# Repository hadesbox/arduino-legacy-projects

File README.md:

# arduino-legacy-projects
This repo is a backup of all my old arduino projects

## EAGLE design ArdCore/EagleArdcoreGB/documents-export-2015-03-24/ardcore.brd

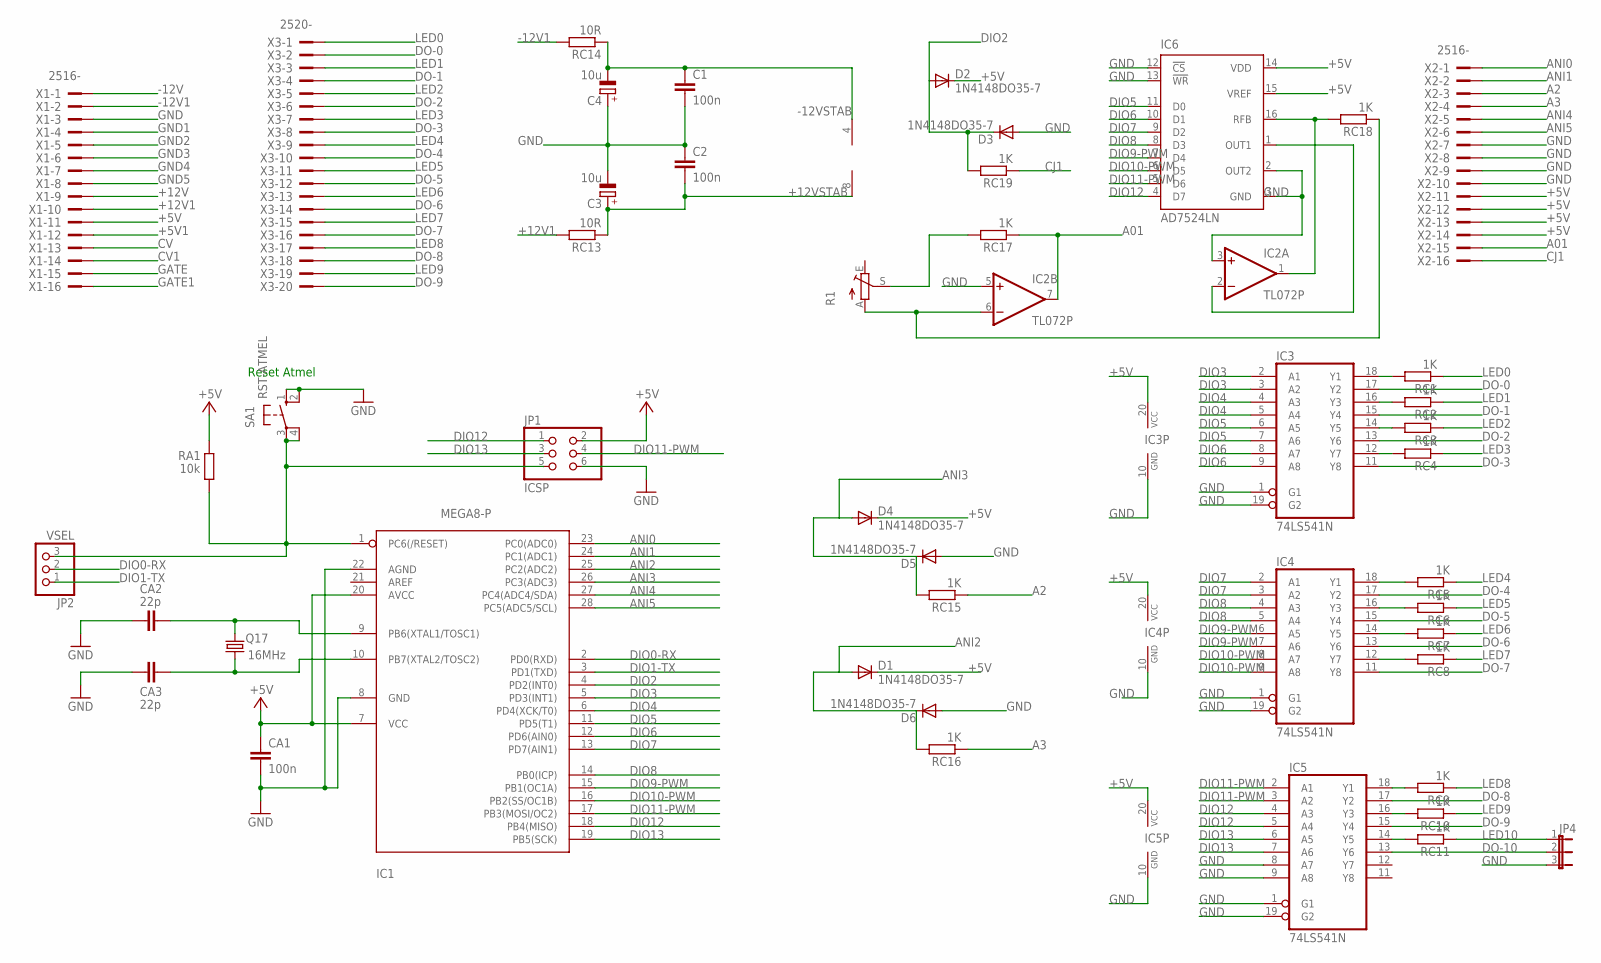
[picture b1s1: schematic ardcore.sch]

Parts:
C1, C2: 100n; C050-025X075
C3, C4: 10u; E2,5-7
CA1: 100n; C050-025X075
CA2, CA3: 22p; C050-025X075
D1, D2, D3, D4, D5, D6: 1N4148DO35-7; DO35-7
IC1: MEGA8-P; DIL28-3
IC2: TL072P; DIL08
IC3, IC4, IC5: 74LS541N; DIL20
IC6: AD7524LN; DIL16
JP1: ICSP; 2X03
JP2: VSEL; 1X03
JP4: JP2E; JP2
Q17: 16MHz; HC49/S
R1: TRIM_EU-B64Y; B64Y
RA1: 10k; 0207/10
RC1, RC2, RC3, RC4, RC5, RC6, RC7, RC8, RC9, RC10, RC11, RC15, RC16, RC17, RC18, RC19: 1K; 0207/10
RC13, RC14: 10R; 0207/10
SA1: RST-ATMEL; B3F-10XX
X1, X2: 2516-; PAK100/2500-16
X3: 2520-; PAK100/2500-20

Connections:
+5V: CA1.1, D1.C, D2.C, D4.C, IC1.7 (VCC), IC1.20 (AVCC), IC3.20 (VCC), IC4.20 (VCC), IC5.20 (VCC), IC6.14 (VDD), IC6.15 (VREF), JP1.2, RA1.1, X1.11, X2.11, X2.12, X2.13, X2.14
+5V1: X1.12
+12V: X1.9
+12V1: RC13.2, X1.10
+12VSTAB: C2.2, C3.+, IC2.8 (V+), RC13.1
-12V: X1.1
-12V1: RC14.2, X1.2
-12VSTAB: C1.1, C4.-, IC2.4 (V-), RC14.1
A01: IC2.7 (OUT), RC17.1, X2.15
A2: RC15.1, X2.3
A3: RC16.1, X2.4
ANI0: IC1.23 (PC0(ADC0)), X2.1
ANI1: IC1.24 (PC1(ADC1)), X2.2
ANI2: D1.A, D6.C, IC1.25 (PC2(ADC2)), RC16.2
ANI3: D4.A, D5.C, IC1.26 (PC3(ADC3)), RC15.2
ANI4: IC1.27 (PC4(ADC4/SDA)), X2.5
ANI5: IC1.28 (PC5(ADC5/SCL)), X2.6
CJ1: RC19.1, X2.16
CV: X1.13
CV1: X1.14
DIO0-RX: IC1.2 (PD0(RXD)), JP2.2
DIO1-TX: IC1.3 (PD1(TXD)), JP2.1
DIO2: D2.A, D3.C, IC1.4 (PD2(INT0)), RC19.2
DIO3: IC1.5 (PD3(INT1)), IC3.2 (A1), IC3.3 (A2)
DIO4: IC1.6 (PD4(XCK/T0)), IC3.4 (A3), IC3.5 (A4)
DIO5: IC1.11 (PD5(T1)), IC3.6 (A5), IC3.7 (A6), IC6.11 (D0)
DIO6: IC1.12 (PD6(AIN0)), IC3.8 (A7), IC3.9 (A8), IC6.10 (D1)
DIO7: IC1.13 (PD7(AIN1)), IC4.2 (A1), IC4.3 (A2), IC6.9 (D2)
DIO8: IC1.14 (PB0(ICP)), IC4.4 (A3), IC4.5 (A4), IC6.8 (D3)
DIO9-PWM: IC1.15 (PB1(OC1A)), IC4.6 (A5), IC4.7 (A6), IC6.7 (D4)
DIO10-PWM: IC1.16 (PB2(SS/OC1B)), IC4.8 (A7), IC4.9 (A8), IC6.6 (D5)
DIO11-PWM: IC1.17 (PB3(MOSI/OC2)), IC5.2 (A1), IC5.3 (A2), IC6.5 (D6), JP1.4
DIO12: IC1.18 (PB4(MISO)), IC5.4 (A3), IC5.5 (A4), IC6.4 (D7), JP1.1
DIO13: IC1.19 (PB5(SCK)), IC5.6 (A5), IC5.7 (A6), JP1.3
DO-0: IC3.17 (Y2), X3.2
DO-1: IC3.15 (Y4), X3.4
DO-2: IC3.13 (Y6), X3.6
DO-3: IC3.11 (Y8), X3.8
DO-4: IC4.17 (Y2), X3.10
DO-5: IC4.15 (Y4), X3.12
DO-6: IC4.13 (Y6), X3.14
DO-7: IC4.11 (Y8), X3.16
DO-8: IC5.17 (Y2), X3.18
DO-9: IC5.15 (Y4), X3.20
DO-10: IC5.13 (Y6), JP4.2
GATE: X1.15
GATE1: X1.16
GND: C1.2, C2.1, C3.-, C4.+, CA1.2, CA2.2, CA3.2, D3.A, D5.A, D6.A, IC1.8 (GND), IC1.22 (AGND), IC2.3 (+IN), IC2.5 (+IN), IC3.1 (G1), IC3.10 (GND), IC3.19 (G2), IC4.1 (G1), IC4.10 (GND), IC4.19 (G2), IC5.1 (G1), IC5.8 (A7), IC5.9 (A8), IC5.10 (GND), IC5.19 (G2), IC6.2 (OUT2), IC6.3 (GND), IC6.12 (!CS), IC6.13 (!WR), JP1.6, JP4.3, SA1.1 (S), SA1.2 (S1), X1.3, X2.7, X2.8, X2.9, X2.10
GND1: X1.4
GND2: X1.5
GND3: X1.6
GND4: X1.7
GND5: X1.8
LED0: RC1.1, X3.1
LED1: RC2.1, X3.3
LED2: RC3.1, X3.5
LED3: RC4.1, X3.7
LED4: RC5.1, X3.9
LED5: RC6.1, X3.11
LED6: RC7.1, X3.13
LED7: RC8.1, X3.15
LED8: RC9.1, X3.17
LED9: RC10.1, X3.19
LED10: JP4.1, RC11.1
unnamed: IC3.18 (Y1), RC1.2
unnamed: IC3.16 (Y3), RC2.2
unnamed: IC3.14 (Y5), RC3.2
unnamed: CA2.1, IC1.9 (PB6(XTAL1/TOSC1)), Q17.2
unnamed: CA3.1, IC1.10 (PB7(XTAL2/TOSC2)), Q17.1
unnamed: IC3.12 (Y7), RC4.2
unnamed: IC4.18 (Y1), RC5.2
unnamed: IC4.16 (Y3), RC6.2
unnamed: IC4.14 (Y5), RC7.2
unnamed: IC4.12 (Y7), RC8.2
unnamed: IC5.18 (Y1), RC9.2
unnamed: IC5.16 (Y3), RC10.2
unnamed: IC5.14 (Y5), RC11.2
unnamed: IC2.6 (-IN), R1.A, RC18.1
unnamed: IC2.2 (-IN), IC6.1 (OUT1)
unnamed: R1.S, RC17.2
unnamed: IC2.1 (OUT), IC6.16 (RFB), RC18.2
RST: IC1.1 (PC6(/RESET)), JP1.5, JP2.3, RA1.2, SA1.3, SA1.4 (P1)

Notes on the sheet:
Reset Atmel

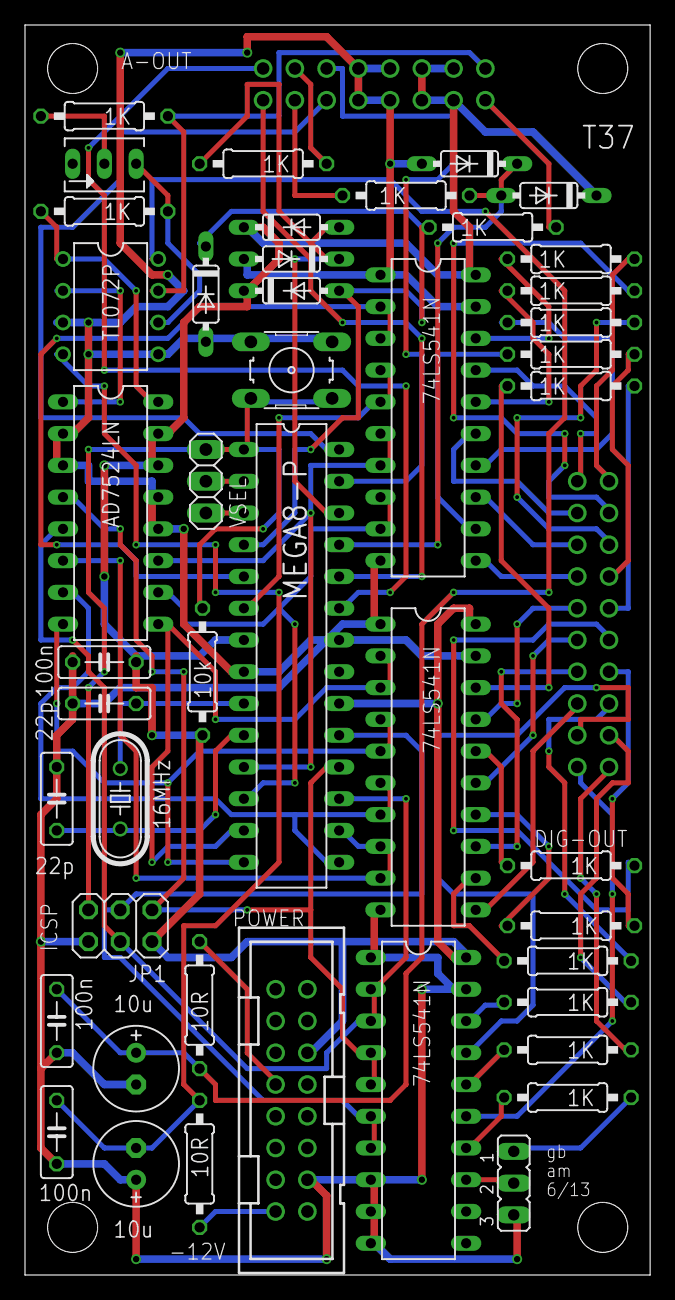
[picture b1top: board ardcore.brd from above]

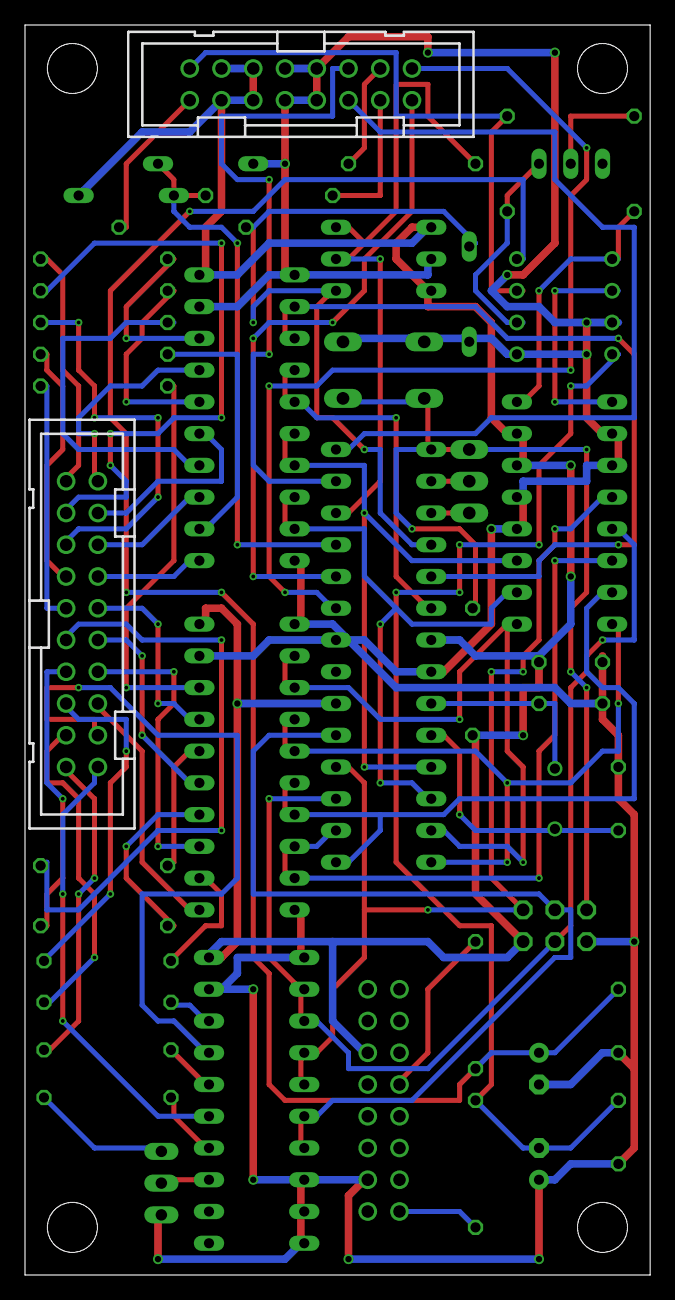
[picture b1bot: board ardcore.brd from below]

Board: 4 copper layers, 50.0 x 100.0 mm, 47 parts (2 on the bottom side), 70 nets.

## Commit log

2017-06-11 Initial commit of all projects in documents folder
2017-06-11 More source files from old dropbox
